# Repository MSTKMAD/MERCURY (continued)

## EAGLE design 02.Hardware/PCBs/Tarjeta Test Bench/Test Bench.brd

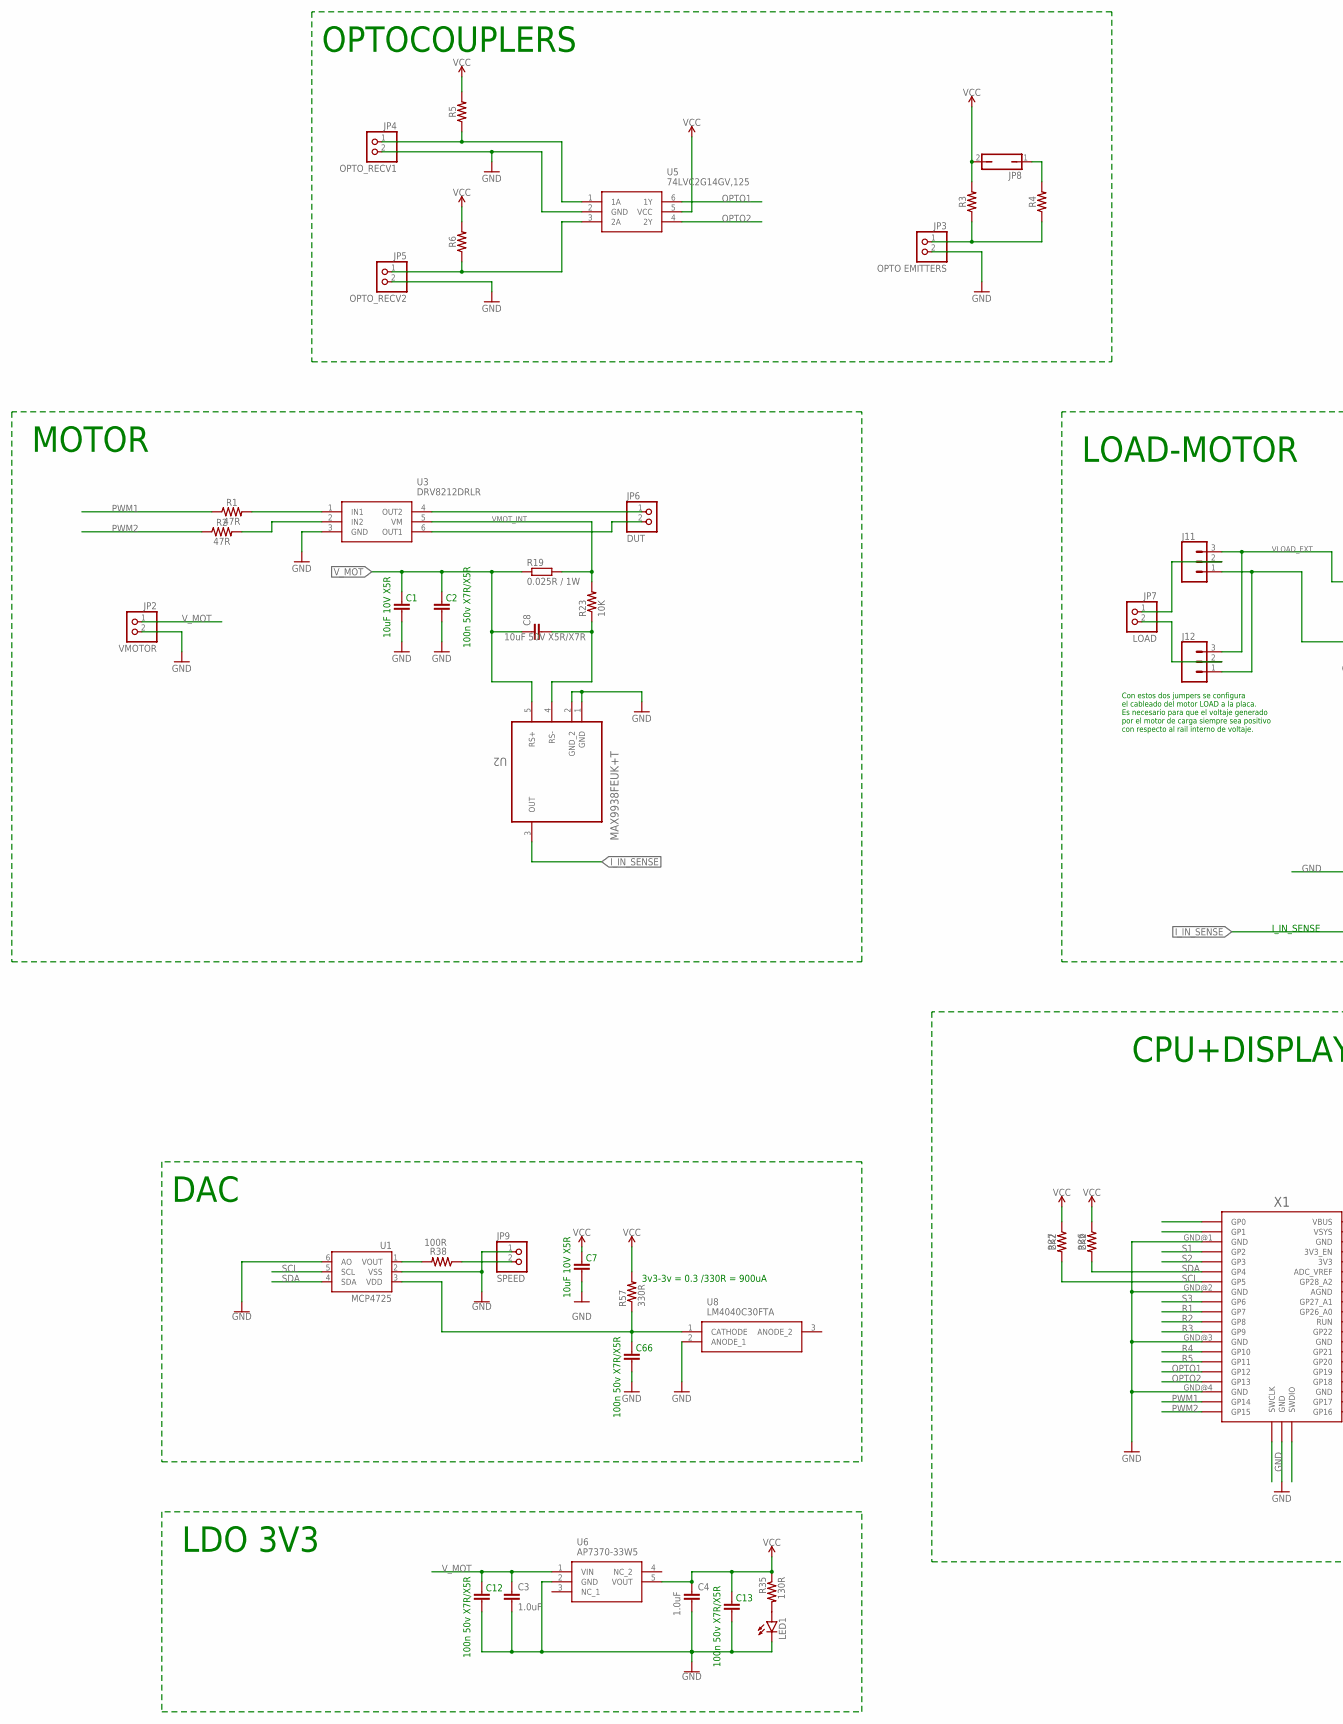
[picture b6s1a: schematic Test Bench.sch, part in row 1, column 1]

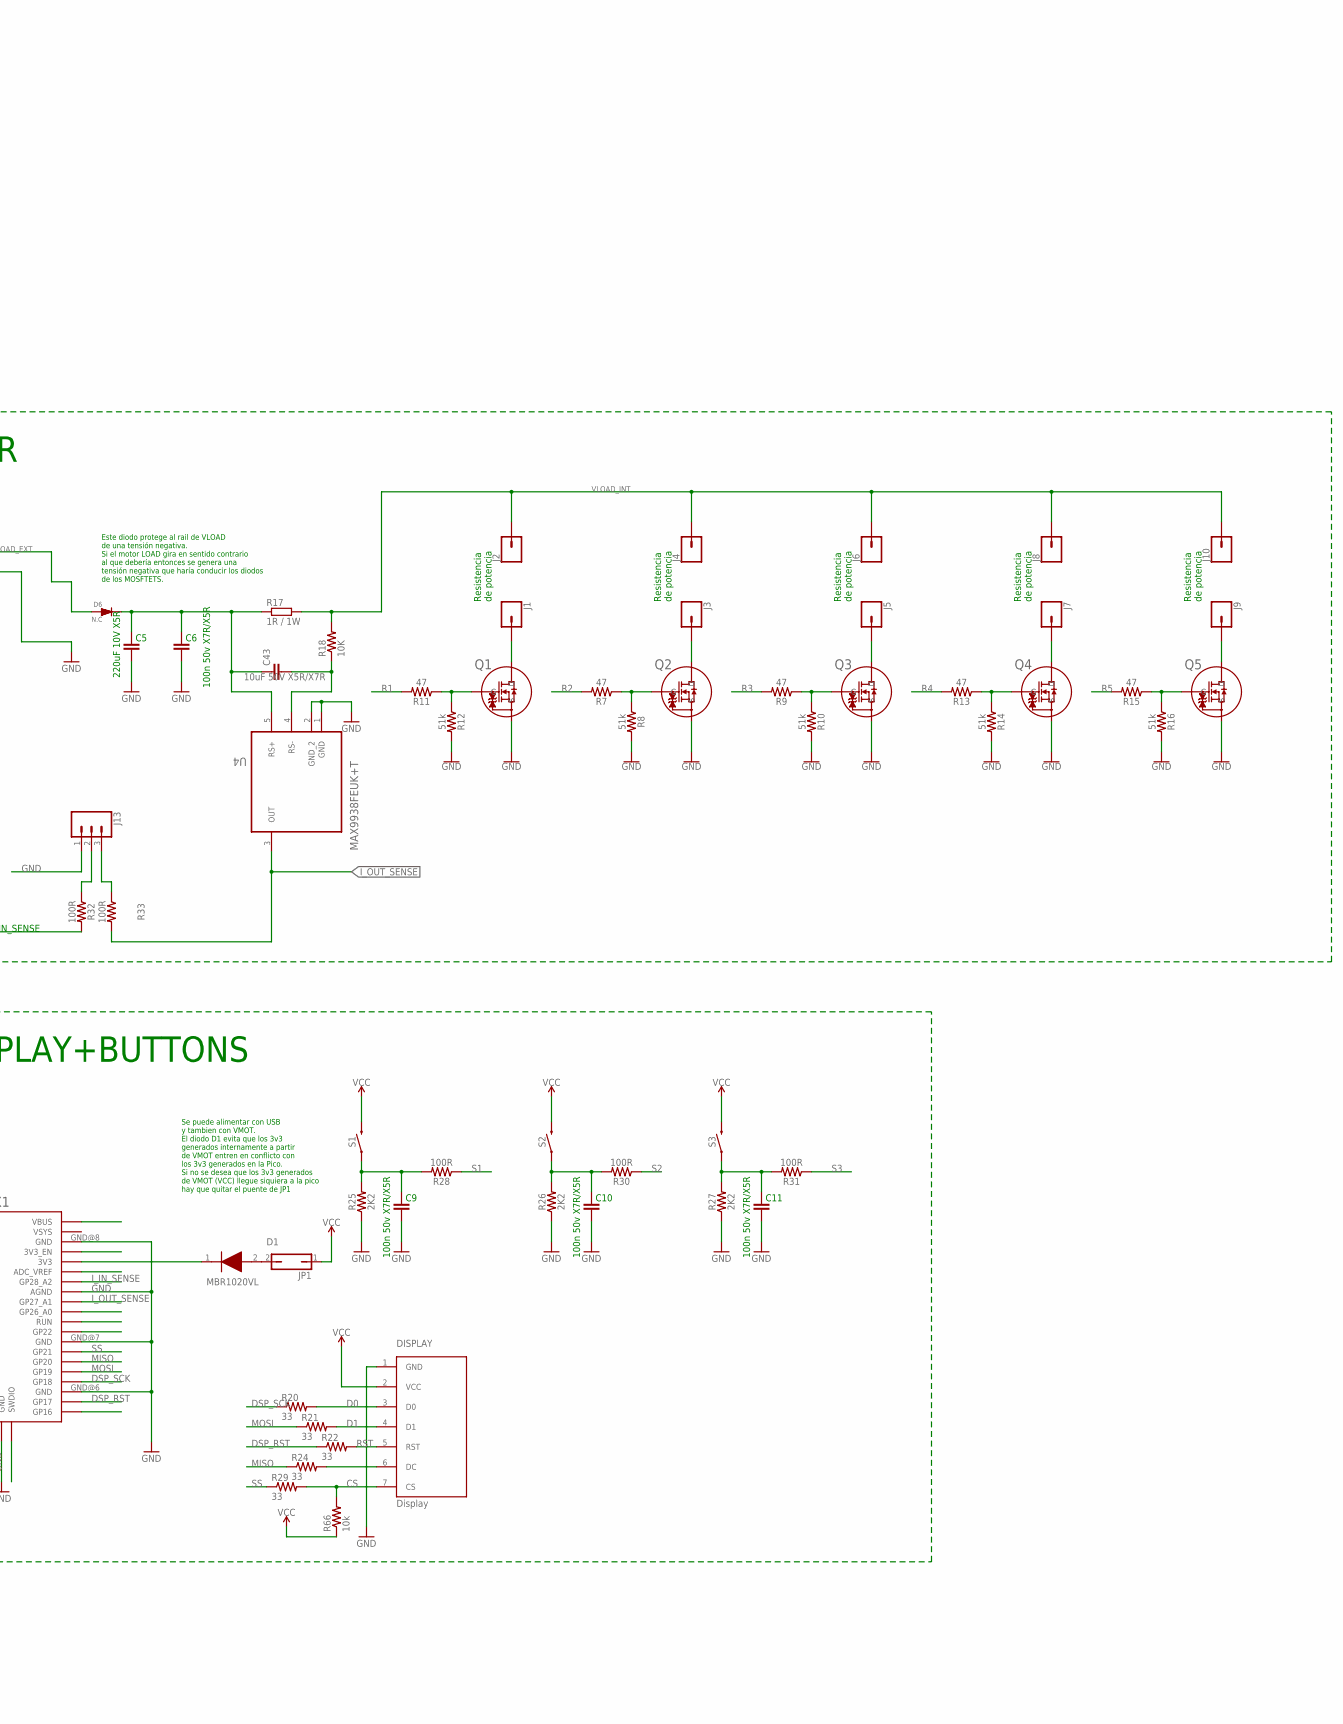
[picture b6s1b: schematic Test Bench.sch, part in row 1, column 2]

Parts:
C1, C7: 10uF 10V X5R; 0805
C2, C6, C9, C10, C11, C12, C13, C66: 100n 50v X7R/X5R; 0805
C3, C4: 1.0uF; 0805
C5: 220uF 10V X5R; 0805
C8, C43: 10uF 50V X5R/X7R; 1206
D1: MBR1020VL; SODFL3617X108N
D6: N.C; DO-214AB
DISPLAY: Display; OLED_LCD
J1, J2, J3, J4, J5, J6, J7, J8, J9, J10: CONN_01; 1X01
J11, J12, J13: CONN_03; 1X03
JP1, JP8: JP1Q; JP1
JP2: VMOTOR; 1X02
JP3: OPTO EMITTERS; 1X02
JP4: OPTO_RECV1; 1X02
JP5: OPTO_RECV2; 1X02
JP6: DUT; 1X02
JP7: LOAD; 1X02
JP9: SPEED; 1X02
LED1: LED3MM
Q1, Q2, Q3, Q4, Q5: PJA3416AE_R1_00001; SOT23_PJA3416_PNJ
R1, R2: 47R; 0805
R3, R4, R5, R6: 0805
R7, R9, R11, R13, R15: 47; 0805
R8, R10, R12, R14, R16: 51k; 0805
R17: 1R / 1W; R2512
R18, R23: 10K; 0805
R19: 0.025R / 1W; R2512
R20, R21, R22, R24, R29: 33; 0805
R25, R26, R27, R36, R37: 2K2; 0805
R28, R30, R31, R32, R33, R38: 100R; 0805
R35: 130R; 0805
R57: 330R; 0805
R66: 10k; 0805
S1, S2, S3: MOMENTARY-SWITCH-SPST-SMD-5.2MM; TACTILE_SWITCH_SMD_5.2MM
U1: MCP4725; SOT23-6
U2, U4: MAX9938FEUK+T; SOT95P280X145-5N
U3: DRV8212DRLR; SOTFL50P160X60-6N
U5: 74LVC2G14GV,125; SOT95P275X110-6N
U6: AP7370-33W5; SOT95P285X140-5N
U8: LM4040C30FTA; SOT96P240X120-3N
X1: RPI_PICO_IG-TH; RPI_PICO_TH

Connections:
3V_REF: C66.2, R57.1, U1.3 (VDD), U8.1 (CATHODE)
CS: DISPLAY.7 (CS), R29.2, R66.2
D0: DISPLAY.3 (D0), R20.2
D1: DISPLAY.4 (D1), R21.2
DSP_RST: R22.1, X1.GP17
DSP_SCK: R20.1, X1.GP18
GND: C1.1, C2.1, C3.2, C4.2, C5.1, C6.1, C7.1, C9.1, C10.1, C11.1, C12.1, C13.1, C66.1, DISPLAY.1 (GND), J11.1, J12.1, J13.1, JP2.2, JP3.2, JP4.2, JP5.2, JP9.1, LED1.K (C), Q1.2 (S), Q2.2 (S), Q3.2 (S), Q4.2 (S), Q5.2 (S), R8.2, R10.2, R12.2, R14.2, R16.2, R25.1, R26.1, R27.1, U1.2 (VSS), U1.6 (AO), U2.1 (GND), U2.2 (GND_2), U3.3 (GND), U4.1 (GND), U4.2 (GND_2), U5.2 (GND), U6.2 (GND), U8.2 (ANODE_1), X1.AGND, X1.GND@1 (GND), X1.GND@2 (GND), X1.GND@3 (GND), X1.GND@4 (GND), X1.GND@5 (GND), X1.GND@6 (GND), X1.GND@7 (GND), X1.GND@8 (GND)
I_IN_SENSE: R32.2, U2.3 (OUT), X1.GP28_A2
I_OUT_SENSE: R33.2, U4.3 (OUT), X1.GP27_A1
MISO: R24.1, X1.GP20
MOSI: R21.1, X1.GP19
unnamed: J13.2, R32.1
unnamed: JP3.1, R3.1, R4.1
unnamed: J9.1, Q5.3 (D)
unnamed: JP8.1, R4.2
unnamed: JP4.1, R5.1, U5.1 (1A)
unnamed: JP5.1, R6.1, U5.3 (2A)
unnamed: JP6.2, U3.6 (OUT1)
unnamed: R38.2, U1.1 (VOUT)
unnamed: J13.3, R33.1
unnamed: JP6.1, U3.4 (OUT2)
unnamed: R1.2, U3.1 (IN1)
unnamed: R2.2, U3.2 (IN2)
unnamed: Q2.1 (G), R7.1, R8.1
unnamed: Q3.1 (G), R9.1, R10.1
unnamed: Q4.1 (G), R13.1, R14.1
unnamed: DISPLAY.6 (DC), R24.2
unnamed: Q5.1 (G), R15.1, R16.1
unnamed: JP9.2, R38.1
unnamed: Q1.1 (G), R11.1, R12.1
unnamed: J11.2, JP7.1
unnamed: D1.2 (A), JP1.2
unnamed: J12.2, JP7.2
unnamed: J1.1, Q1.3 (D)
unnamed: J3.1, Q2.3 (D)
unnamed: J5.1, Q3.3 (D)
unnamed: J7.1, Q4.3 (D)
unnamed: C9.2, R25.2, R28.2, S1.1
unnamed: C10.2, R26.2, R30.2, S2.1
unnamed: C43.2, R18.1, U4.4 (RS-)
unnamed: D1.1 (K), X1.3V3
unnamed: C8.2, R23.1, U2.4 (RS-)
unnamed: LED1.A, R35.2
unnamed: C11.2, R27.2, R31.2, S3.1
OPTO1: U5.6 (1Y), X1.GP12
OPTO2: U5.4 (2Y), X1.GP13
PWM1: R1.1, X1.GP14
PWM2: R2.1, X1.GP15
R1: R11.2, X1.GP7
R2: R7.2, X1.GP8
R3: R9.2, X1.GP9
R4: R13.2, X1.GP10
R5: R15.2, X1.GP11
RST: DISPLAY.5 (RST), R22.2
S1: R28.1, X1.GP2
S2: R30.1, X1.GP3
S3: R31.1, X1.GP6
SCL: R37.2, U1.5 (SCL), X1.GP5
SDA: R36.2, U1.4 (SDA), X1.GP4
SS: R29.1, X1.GP21
VCC: C4.1, C7.2, C13.2, DISPLAY.2 (VCC), JP1.1, JP8.2, R3.2, R5.2, R6.2, R35.1, R36.1, R37.1, R57.2, R66.1, S1.3 (2), S2.3 (2), S3.3 (2), U5.5 (VCC), U6.5 (VOUT)
VLOAD_EXT: D6.1 (A), J11.3, J12.3
VLOAD_INT: J2.1, J4.1, J6.1, J8.1, J10.1, R17.2, R18.2
VMOT_INT: R19.2, R23.2, U3.5 (VM)
VOLAD_EXT2: C5.2, C6.2, C43.1, D6.2 (K), R17.1, U4.5 (RS+)
V_MOT: C1.2, C2.2, C3.1, C8.1, C12.2, JP2.1, R19.1, U2.5 (RS+), U6.1 (VIN)

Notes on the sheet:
Resistencia de potencia
3v3-3v = 0.3 /330R = 900uA
I_IN_SENSE
DAC
MOTOR
OPTOCOUPLERS
LOAD-MOTOR
CPU+DISPLAY+BUTTONS
LDO 3V3
Se puede alimentar con USB y tambien con VMOT. El diodo D1 evita que los 3v3 generados internamente a partir de VMOT entren en conflicto con los 3v3 generados en la Pico. Si no se desea que los 3v3 generados de VMOT (VCC) llegue siquiera a la pico hay que quitar el puente de JP1
Este diodo protege al rail de VLOAD de una tensión negativa. Si el motor LOAD gira en sentido contrario al que debería entonces se genera una tensión negativa que haría conducir los diodos de los MOSFTETS.
Con estos dos jumpers se configura el cableado del motor LOAD a la placa. Es necesario para que el voltaje generado por el motor de carga siempre sea positivo con respecto al rail interno de voltaje.

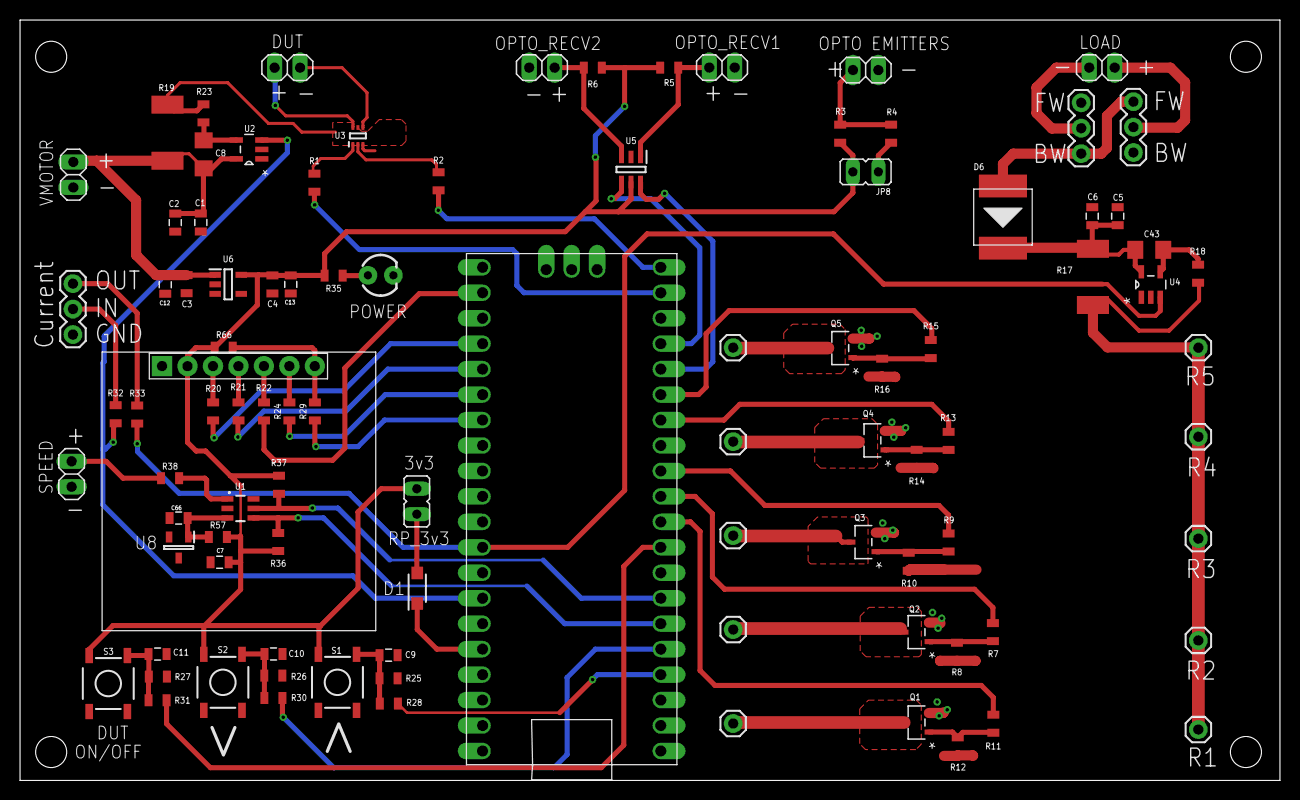
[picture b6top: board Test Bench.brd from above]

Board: 2 copper layers, 125.7 x 75.9 mm, 96 parts (0 on the bottom side), 66 nets.
